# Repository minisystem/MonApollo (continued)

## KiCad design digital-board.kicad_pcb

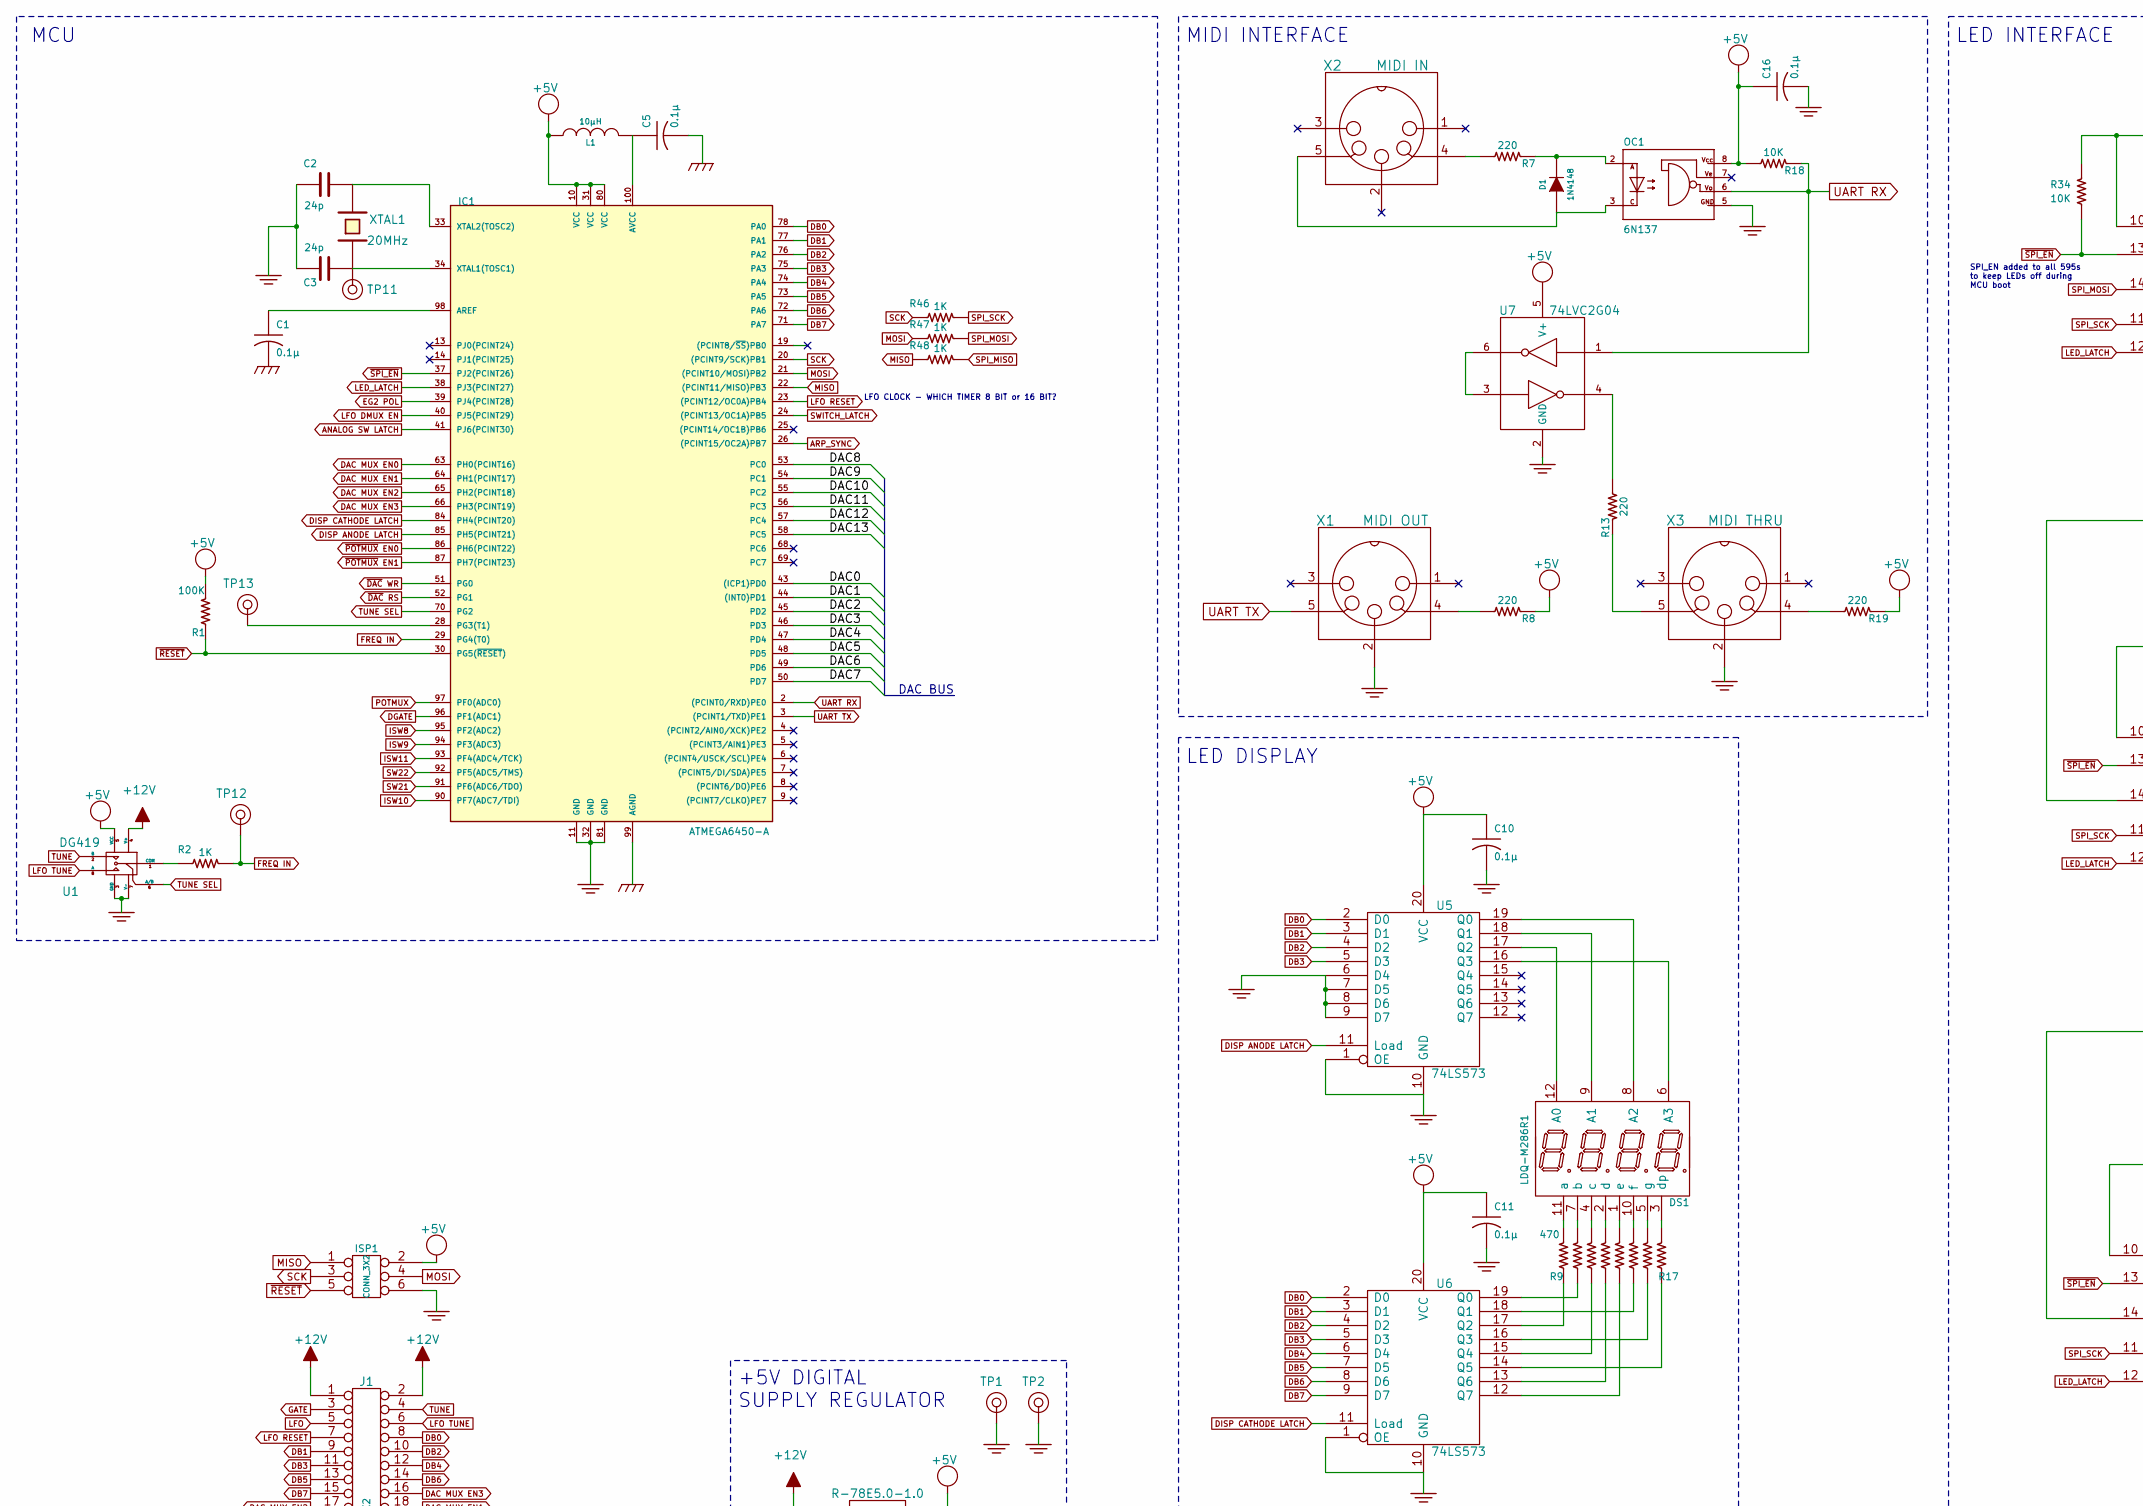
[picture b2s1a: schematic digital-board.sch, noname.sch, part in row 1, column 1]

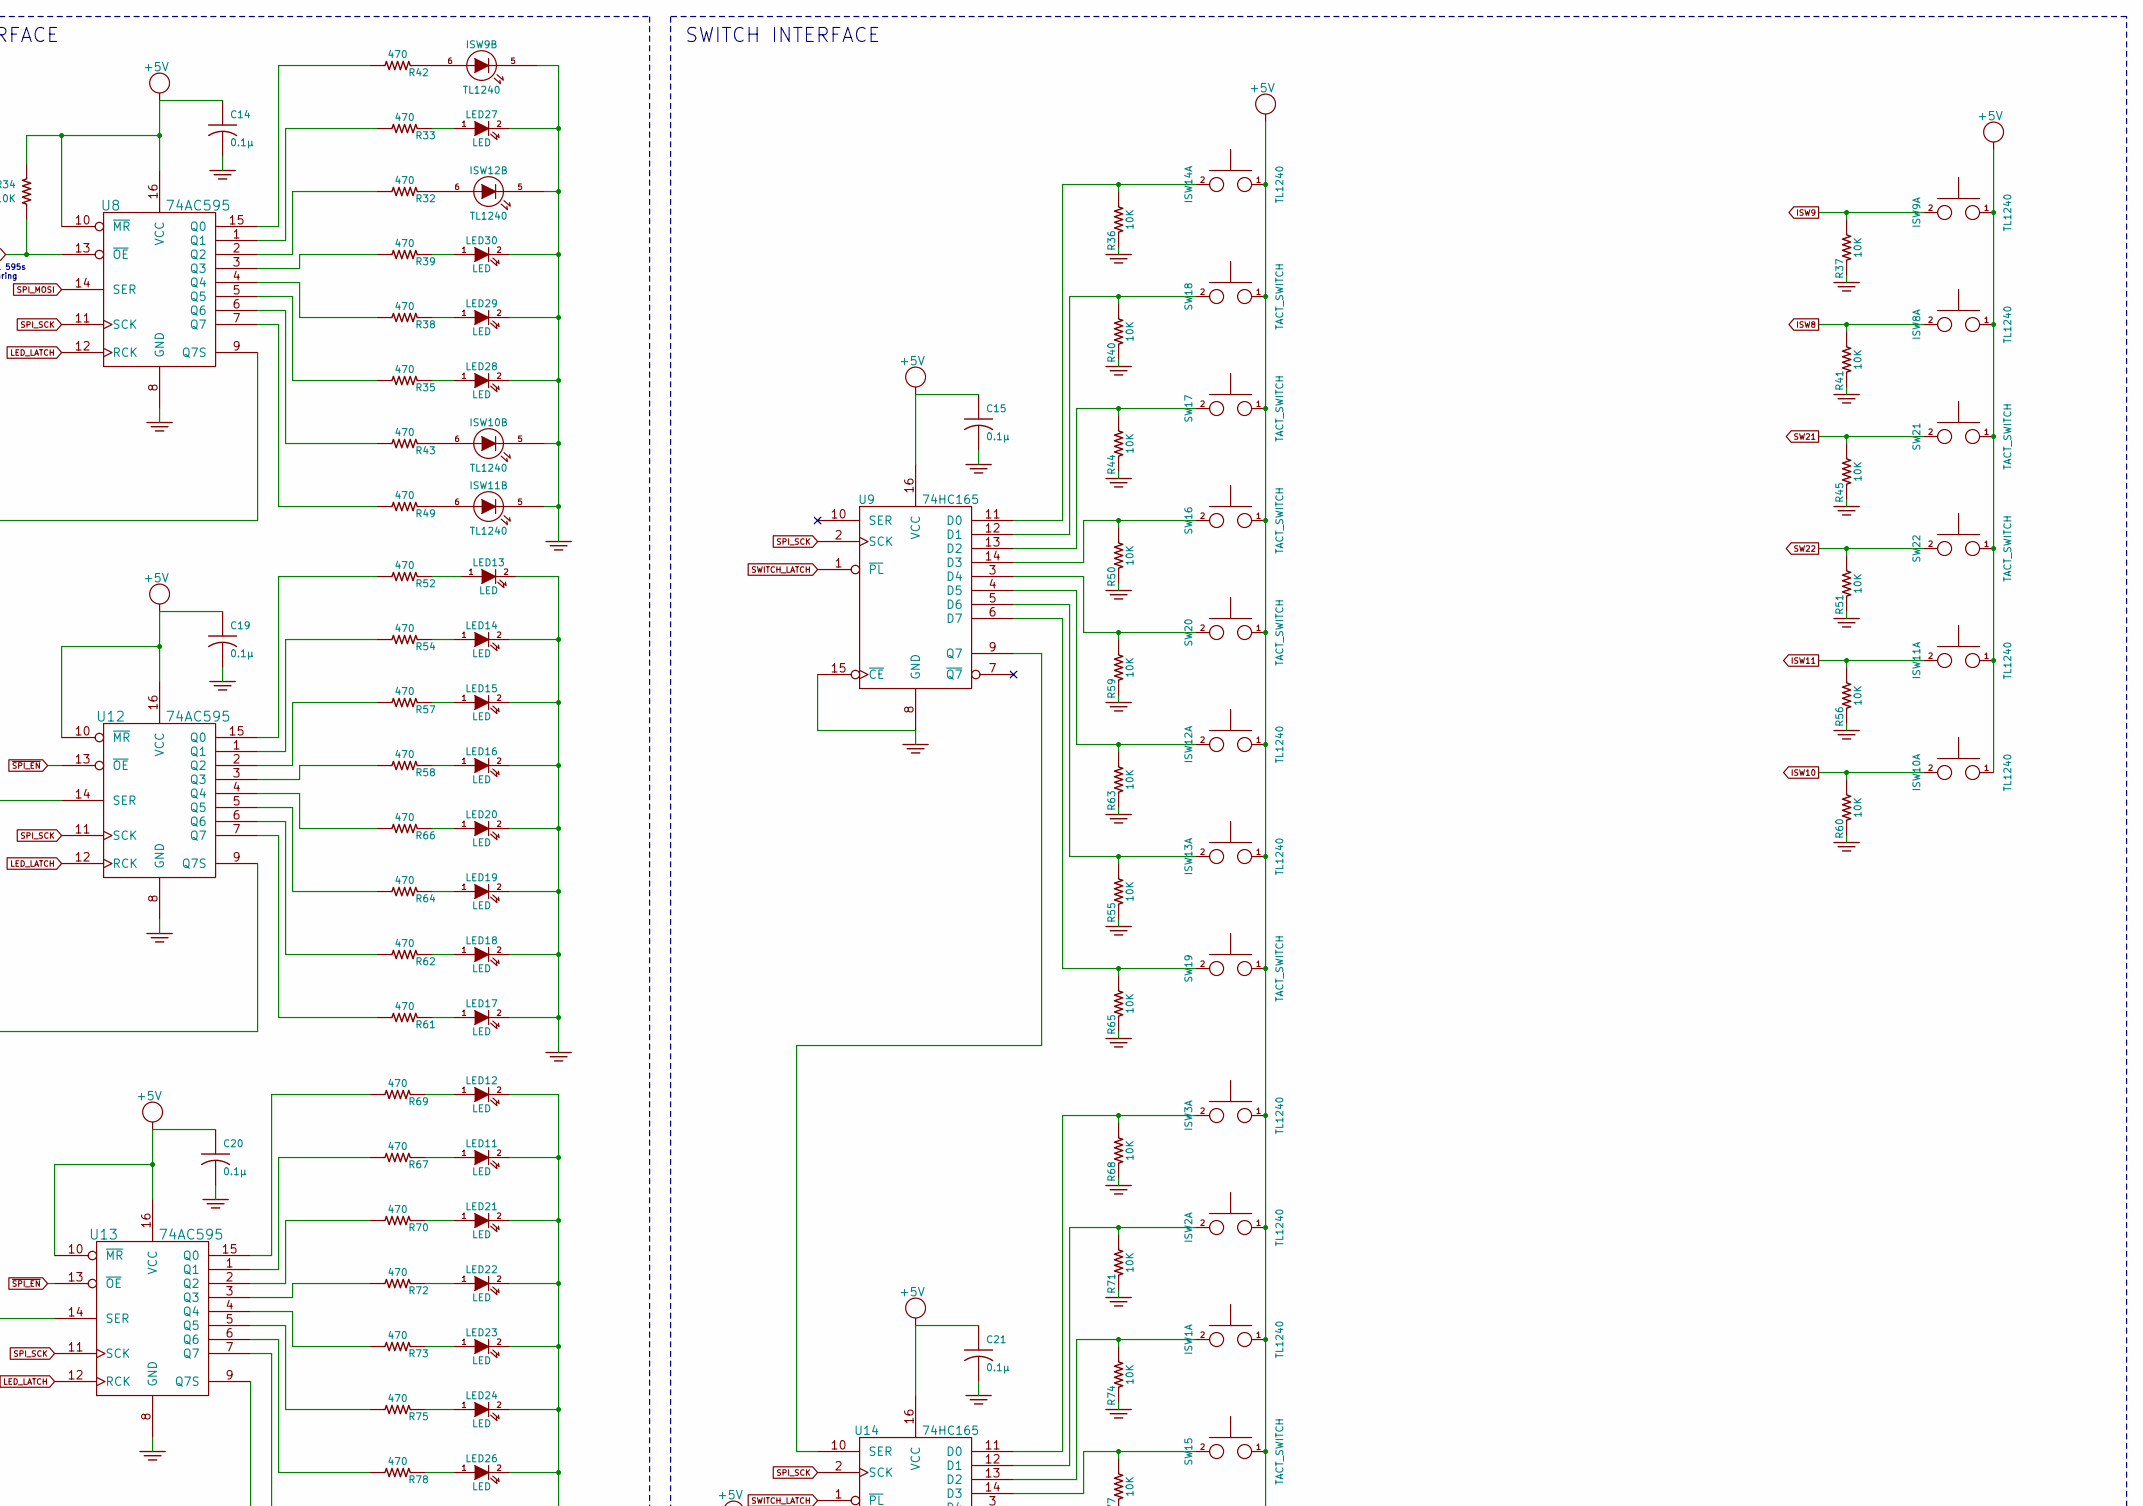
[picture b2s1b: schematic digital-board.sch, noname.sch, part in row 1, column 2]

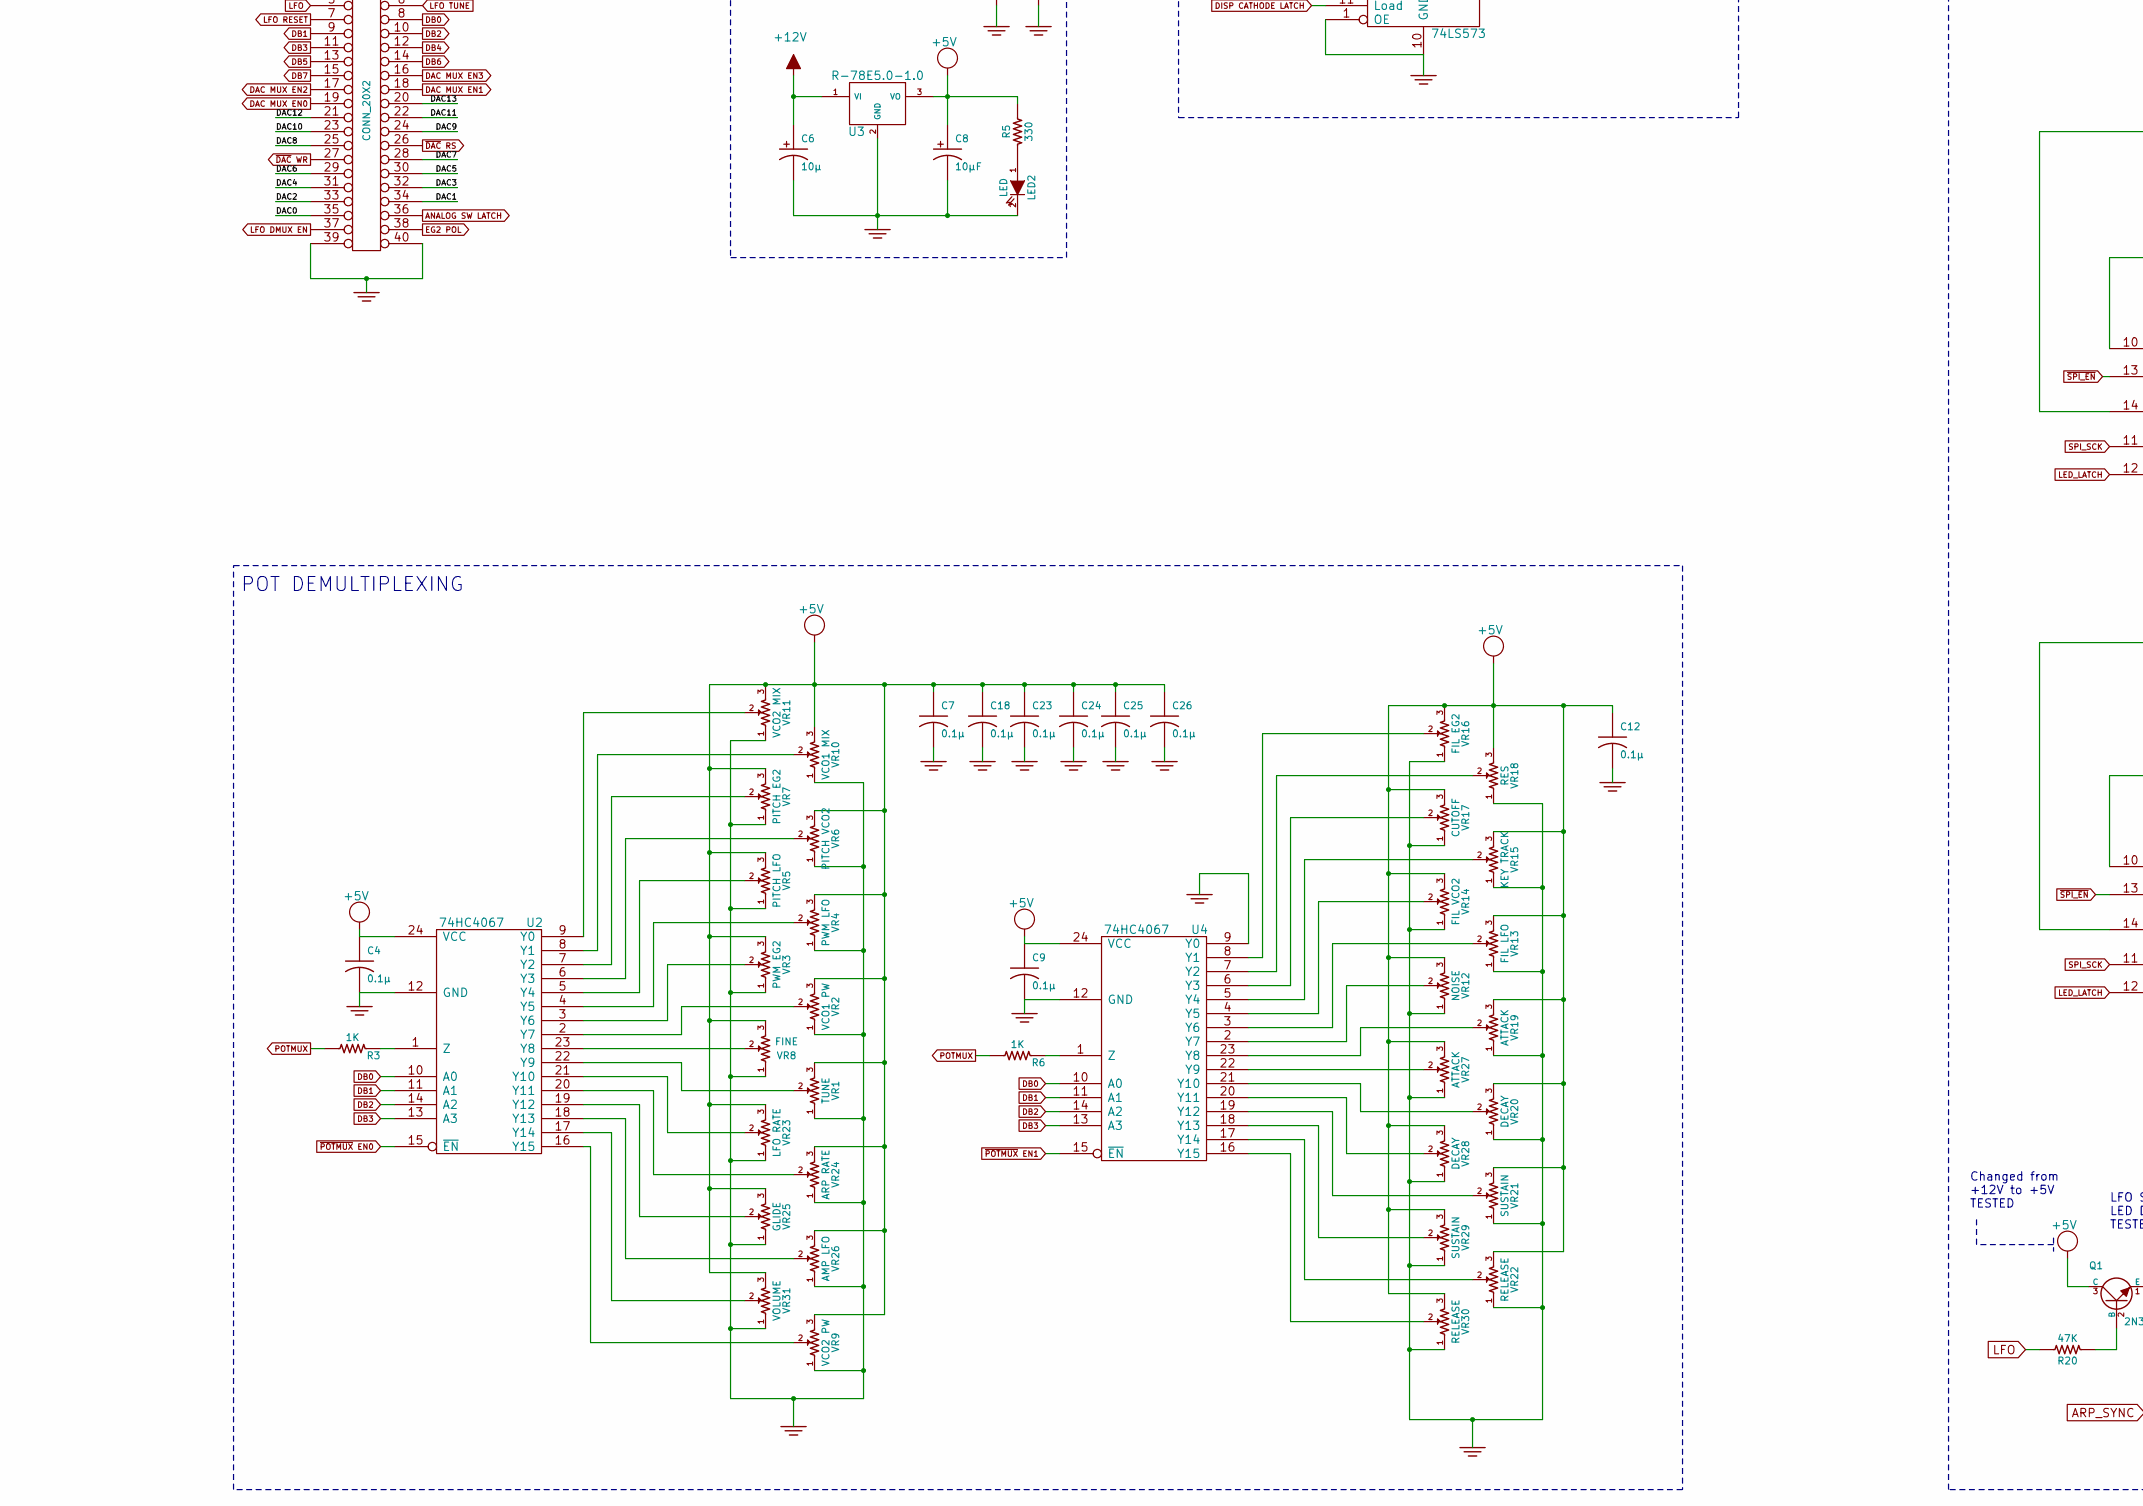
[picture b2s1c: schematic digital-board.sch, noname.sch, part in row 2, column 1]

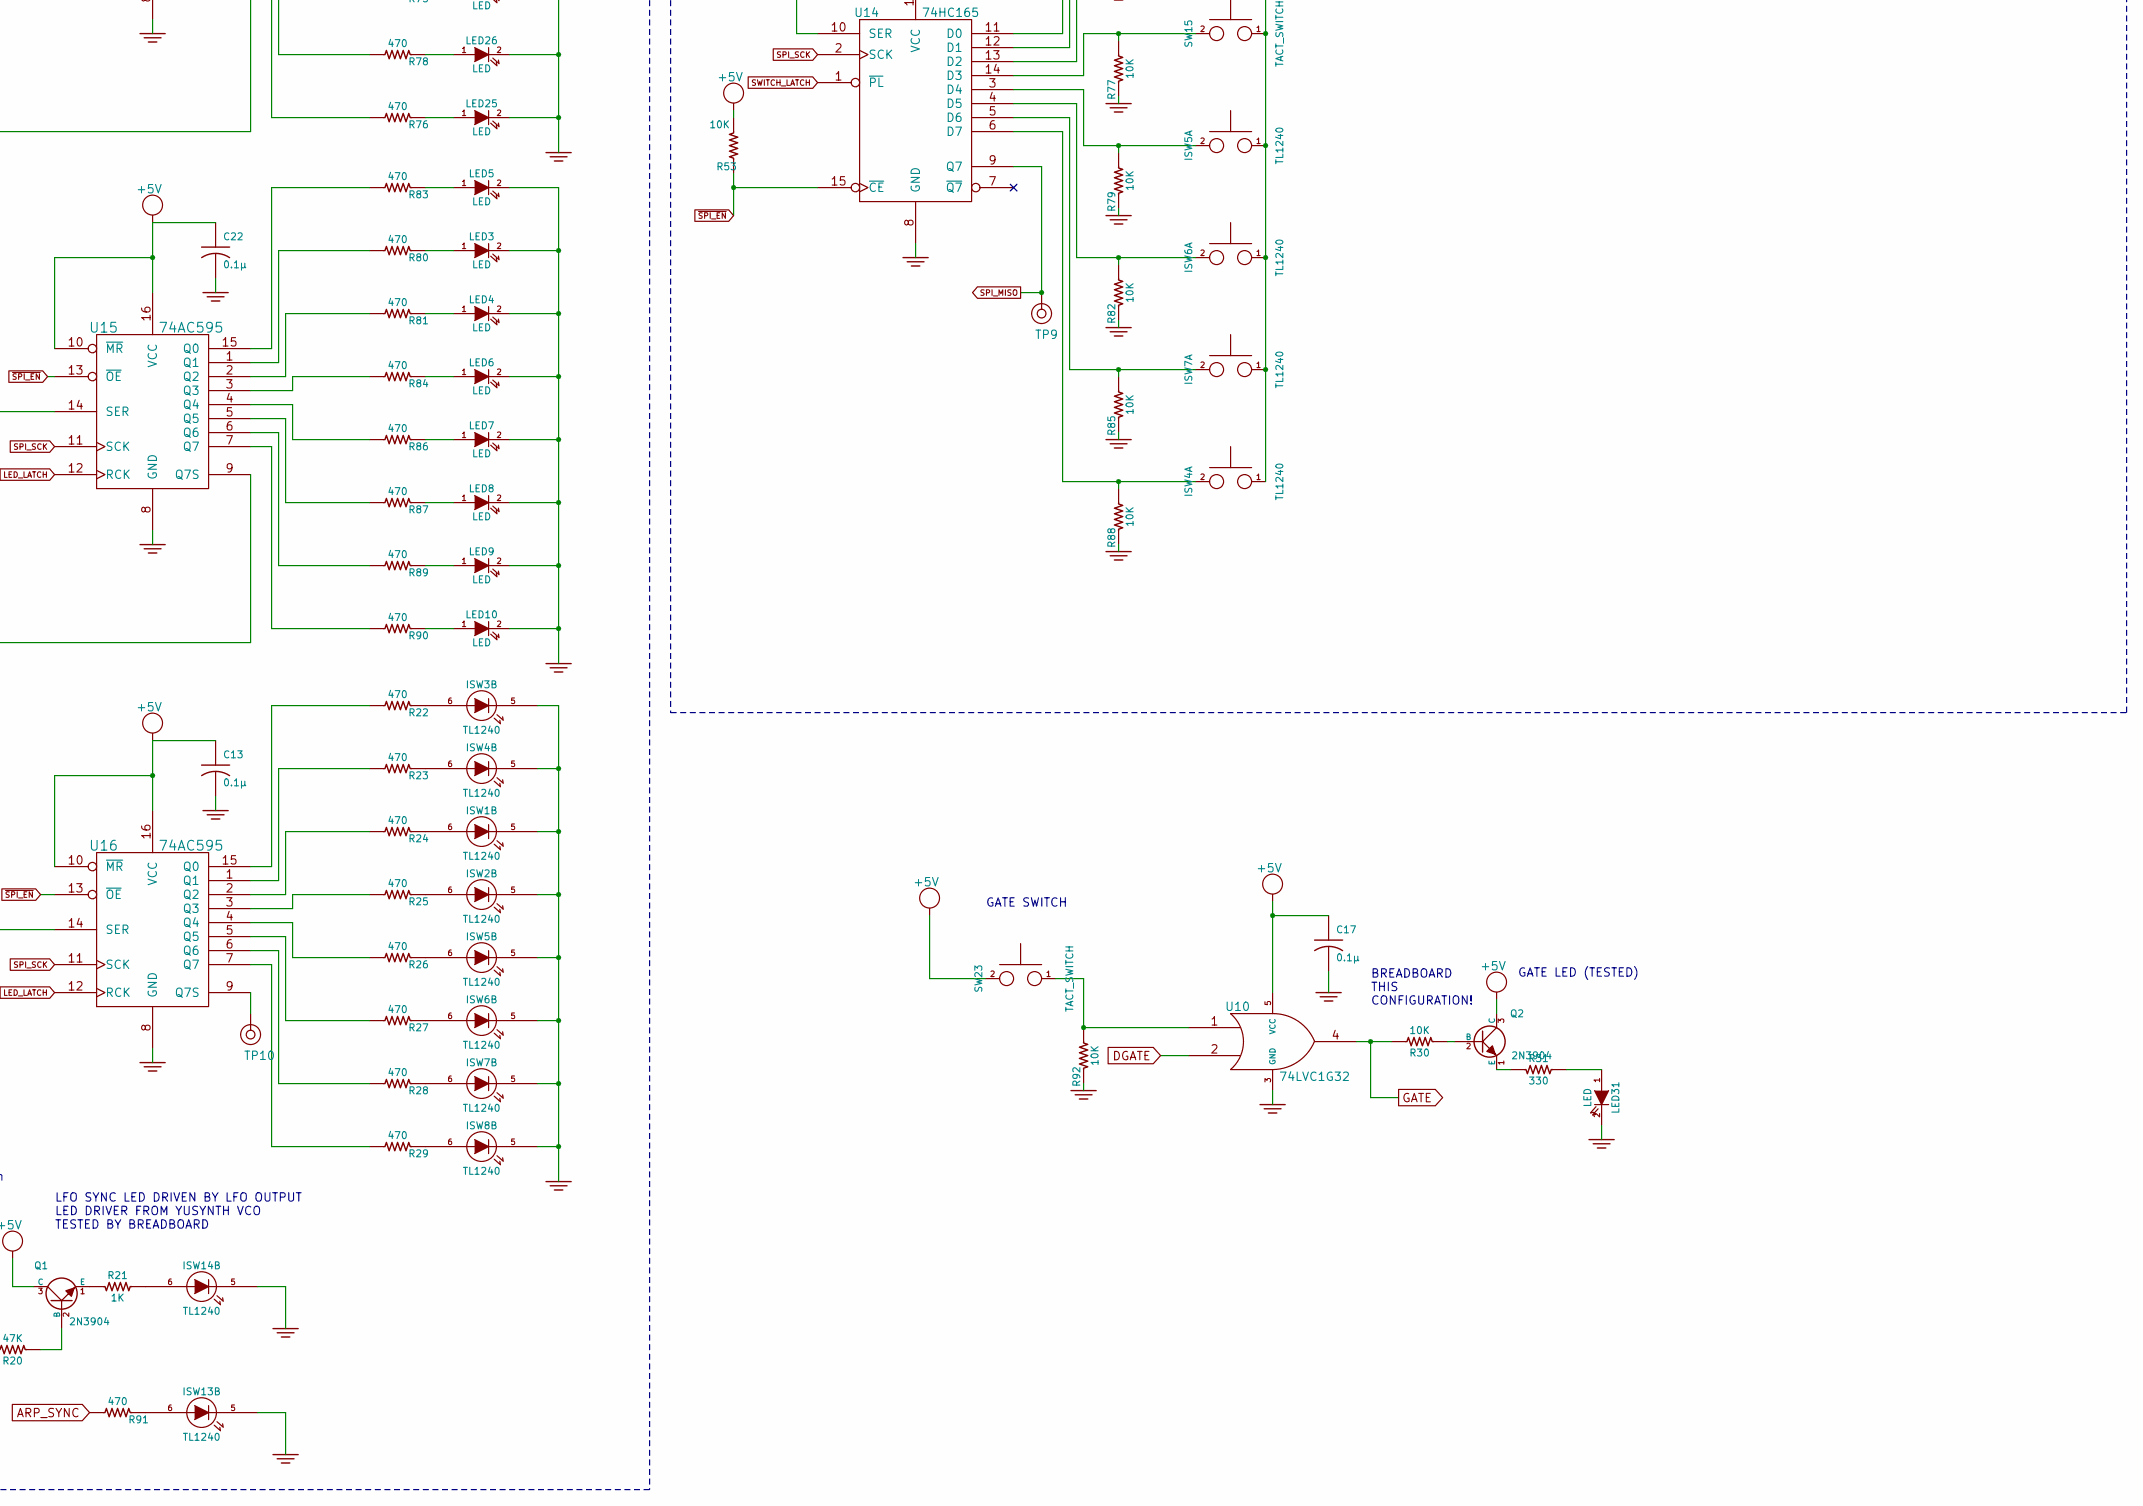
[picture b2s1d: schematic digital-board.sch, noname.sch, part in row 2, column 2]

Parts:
C1, C4, C5, C7, C9, C10, C11, C12, C13, C14, C15, C16, C17, C18, C19, C20, C21, C22, C23, C24, C25, C26: 0.1µ
C2, C3: 24p
C6: 10µ
C8: 10µF
D1: 1N4148
DS1: LDQ-M286R1; 7-segment-4-digit
IC1: ATMEGA6450-A; TQFP100
ISP1: CONN_3X2
ISW1, ISW2, ISW3, ISW4, ISW5, ISW6, ISW7, ISW8, ISW9, ISW10, ISW11, ISW12, ISW13, ISW14: TL1240
J1: CONN_20X2
L1: 10µH
LED2, LED31: LED
LED3, LED4, LED5, LED6, LED7, LED8, LED9, LED10, LED11, LED12, LED13, LED14, LED15, LED16, LED17, LED18, LED19, LED20, LED21, LED22, LED23, LED24, LED25, LED26, LED27, LED28, LED29, LED30: LED
OC1: 6N137; optocoupler-DIL08
Q1, Q2: 2N3904
R1: 100K
R2, R3, R6, R46, R47, R48: 1K
R5, R31: 330
R7, R8, R13, R19: 220
R9, R22, R23, R24, R25, R26, R27, R28, R29, R32, R33, R35, R38, R39, R42, R43, R49, R52, R54, R57, R58, R61, R62, R64, R66, R67, R69, R70, R72, R73, R75, R76, R78, R80, R81, R83, R84, R86, R87, R89, R90, R91: 470
R10, R11, R12, R14, R15, R16, R17: 560
R18, R34, R36, R37, R40, R41, R44, R45, R50, R51, R53, R55, R56, R59, R60, R63, R65, R68, R71, R74, R77, R79, R82, R85, R88, R92: 10K
R20: 47K
R21: 1K
R30: 10K
SW15, SW16, SW17, SW18, SW19, SW20, SW21, SW22, SW23: TACT_SWITCH
TP1, TP2, TP9, TP10, TP12, TP13: CONN_1
TP11: CONN_1
U1: DG419
U2, U4: 74HC4067
U3: R-78E5.0-1.0
U5, U6: 74LS573
U7: 74LVC2G04
U8, U12, U13, U15, U16: 74AC595
U9, U14: 74HC165
U10: 74LVC1G32
VR1: TUNE
VR2: VCO1 PW
VR3: PWM EG2
VR4: PWM LFO
VR5: PITCH LFO
VR6: PITCH VCO2
VR7: PITCH EG2
VR8: FINE
VR9: VCO2 PW
VR10: VCO1 MIX
VR11: VCO2 MIX
VR12: NOISE
VR13: FIL LFO
VR14: FIL VCO2
VR15: KEY TRACK
VR16: FIL EG2
VR17: CUTOFF
VR18: RES
VR19, VR27: ATTACK
VR20, VR28: DECAY
VR21, VR29: SUSTAIN
VR22, VR30: RELEASE
VR23: LFO RATE
VR24: ARP RATE
VR25: GLIDE
VR26: AMP LFO
VR31: VOLUME
X1: MIDI OUT
X2: MIDI IN
X3: MIDI THRU
XTAL1: 20MHz

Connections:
+5V: C4.1, C7.1, C8.1 (+), C9.1, C10.1, C11.1, C12.1, C13.1, C14.1, C15.1, C16.1, C17.1, C18.1, C19.1, C20.1, C21.1, C22.1, C23.1, C24.1, C25.1, C26.1, IC1.10 (VCC), IC1.31 (VCC), IC1.80 (VCC), ISP1.2, ISW1.1, ISW2.1, ISW3.1, ISW4.1, ISW5.1, ISW6.1, ISW7.1, ISW8.1, ISW9.1, ISW10.1, ISW11.1, ISW12.1, ISW13.1, ISW14.1, L1.1, OC1.8, Q1.3 (C), Q2.3 (C), R1.1, R5.2, R8.1, R18.2, R19.1, R34.1, R53.1, SW15.1, SW16.1, SW17.1, SW18.1, SW19.1, SW20.1, SW21.1, SW22.1, SW23.2, U1.5 (VCC), U2.24 (VCC), U3.3 (VO), U4.24 (VCC), U5.20 (VCC), U6.20 (VCC), U7.5 (V+), U8.10 (~MR), U8.16 (VCC), U9.16 (VCC), U10.5 (VCC), U12.10 (~MR), U12.16 (VCC), U13.10 (~MR), U13.16 (VCC), U14.16 (VCC), U15.10 (~MR), U15.16 (VCC), U16.10 (~MR), U16.16 (VCC), VR1.3, VR2.3, VR3.3, VR4.3, VR5.3, VR6.3, VR7.3, VR8.3, VR9.3, VR10.3, VR11.3, VR12.3, VR13.3, VR14.3, VR15.3, VR16.3, VR17.3, VR18.3, VR19.3, VR20.3, VR21.3, VR22.3, VR23.3, VR24.3, VR25.3, VR26.3, VR27.3, VR28.3, VR29.3, VR30.3, VR31.3
+12V: C6.1 (+), J1.1, J1.2, U1.4 (V+), U3.1 (VI)
/DAC0: IC1.43 ((ICP1)PD0), J1.35
/DAC1: IC1.44 ((INT0)PD1), J1.34
/DAC2: IC1.45 (PD2), J1.33
/DAC3: IC1.46 (PD3), J1.32
/DAC4: IC1.47 (PD4), J1.31
/DAC5: IC1.48 (PD5), J1.30
/DAC6: IC1.49 (PD6), J1.29
/DAC7: IC1.50 (PD7), J1.28
/DAC8: IC1.53 (PC0), J1.25
/DAC9: IC1.54 (PC1), J1.24
/DAC10: IC1.55 (PC2), J1.23
/DAC11: IC1.56 (PC3), J1.22
/DAC12: IC1.57 (PC4), J1.21
/DAC13: IC1.58 (PC5), J1.20
ANALOG SW LATCH: IC1.41 (PJ6(PCINT30)), J1.36
ARP_SYNC: IC1.26 ((PCINT15/OC2A)PB7), R91.2
DAC MUX EN0: IC1.63 (PH0(PCINT16)), J1.19
DAC MUX EN1: IC1.64 (PH1(PCINT17)), J1.18
DAC MUX EN2: IC1.65 (PH2(PCINT18)), J1.17
DAC MUX EN3: IC1.66 (PH3(PCINT19)), J1.16
DB0: IC1.78 (PA0), J1.8, U2.10 (A0), U4.10 (A0), U5.2 (D0), U6.2 (D0)
DB1: IC1.77 (PA1), J1.9, U2.11 (A1), U4.11 (A1), U5.3 (D1), U6.3 (D1)
DB2: IC1.76 (PA2), J1.10, U2.14 (A2), U4.14 (A2), U5.4 (D2), U6.4 (D2)
DB3: IC1.75 (PA3), J1.11, U2.13 (A3), U4.13 (A3), U5.5 (D3), U6.5 (D3)
DB4: IC1.74 (PA4), J1.12, U6.6 (D4)
DB5: IC1.73 (PA5), J1.13, U6.7 (D5)
DB6: IC1.72 (PA6), J1.14, U6.8 (D6)
DB7: IC1.71 (PA7), J1.15, U6.9 (D7)
DGATE: IC1.96 (PF1(ADC1)), U10.2
DISP ANODE LATCH: IC1.85 (PH5(PCINT21)), U5.11 (Load)
DISP CATHODE LATCH: IC1.84 (PH4(PCINT20)), U6.11 (Load)
EG2 POL: IC1.39 (PJ4(PCINT28)), J1.38
FREQ IN: IC1.29 (PG4(T0)), R2.1, TP12.1
GATE: J1.3, R30.2, U10.4
ISW8: IC1.95 (PF2(ADC2)), ISW8.2, R41.2
ISW9: IC1.94 (PF3(ADC3)), ISW9.2, R37.2
ISW10: IC1.90 (PF7(ADC7/TDI)), ISW10.2, R60.2
ISW11: IC1.93 (PF4(ADC4/TCK)), ISW11.2, R56.2
LED_LATCH: IC1.38 (PJ3(PCINT27)), U8.12 (RCK), U12.12 (RCK), U13.12 (RCK), U15.12 (RCK), U16.12 (RCK)
LFO: J1.5, R20.2
LFO DMUX EN: IC1.40 (PJ5(PCINT29)), J1.37
LFO RESET: IC1.23 ((PCINT12/OC0A)PB4), J1.7
LFO TUNE: J1.6, U1.8 (A)
MISO: IC1.22 ((PCINT11/MISO)PB3), ISP1.1, R48.2
MOSI: IC1.21 ((PCINT10/MOSI)PB2), ISP1.4, R47.2
unnamed: C1.1, IC1.98 (AREF)
unnamed: C2.2, IC1.33 (XTAL2(TOSC2)), XTAL1.2
unnamed: C3.2, IC1.34 (XTAL1(TOSC1)), TP11.1, XTAL1.1
unnamed: C5.1, IC1.100 (AVCC), L1.2
unnamed: D1.1 (A), OC1.3, X2.5
unnamed: D1.2 (K), OC1.2, R7.1
unnamed: DS1.1 (e), R14.1
unnamed: DS1.2 (d), R12.1
unnamed: DS1.3 (dp), R17.1
unnamed: DS1.4 (c), R11.1
unnamed: DS1.5 (g), R16.1
unnamed: DS1.6 (A3), U5.16 (Q3)
unnamed: DS1.7 (b), R10.1
unnamed: DS1.8 (A2), U5.19 (Q0)
unnamed: DS1.9 (A1), U5.18 (Q1)
unnamed: DS1.10 (f), R15.1
unnamed: DS1.11 (a), R9.1
unnamed: DS1.12 (A0), U5.17 (Q2)
unnamed: IC1.28 (PG3(T1)), TP13.1
unnamed: ISW1.2, R74.2, U14.13 (D2)
unnamed: ISW1.6 (A), R24.1
unnamed: ISW2.2, R71.2, U14.12 (D1)
unnamed: ISW2.6 (A), R25.1
unnamed: ISW3.2, R68.2, U14.11 (D0)
unnamed: ISW3.6 (A), R22.1
unnamed: ISW4.2, R88.2, U14.6 (D7)
unnamed: ISW4.6 (A), R23.1
unnamed: ISW5.2, R79.2, U14.3 (D4)
unnamed: ISW5.6 (A), R26.1
unnamed: ISW6.2, R82.2, U14.4 (D5)
unnamed: ISW6.6 (A), R27.1
unnamed: ISW7.2, R85.2, U14.5 (D6)
unnamed: ISW7.6 (A), R28.1
unnamed: ISW8.6 (A), R29.1
unnamed: ISW9.6 (A), R42.1
unnamed: ISW10.6 (A), R43.1
unnamed: ISW11.6 (A), R49.1
unnamed: ISW12.2, R63.2, U9.4 (D5)
unnamed: ISW12.6 (A), R32.1
unnamed: ISW13.2, R55.2, U9.5 (D6)
unnamed: ISW13.6 (A), R91.1
unnamed: ISW14.2, R36.2, U9.11 (D0)
unnamed: ISW14.6 (A), R21.2
unnamed: LED2.1 (A), R5.1
unnamed: LED3.1 (A), R80.1
unnamed: LED4.1 (A), R81.1
unnamed: LED5.1 (A), R83.1
unnamed: LED6.1 (A), R84.1
unnamed: LED7.1 (A), R86.1
unnamed: LED8.1 (A), R87.1
unnamed: LED9.1 (A), R89.1
unnamed: LED10.1 (A), R90.1
unnamed: LED11.1 (A), R67.1
unnamed: LED12.1 (A), R69.1
unnamed: LED13.1 (A), R52.1
unnamed: LED14.1 (A), R54.1
unnamed: LED15.1 (A), R57.1
unnamed: LED16.1 (A), R58.1
unnamed: LED17.1 (A), R61.1
unnamed: LED18.1 (A), R62.1
unnamed: LED19.1 (A), R64.1
unnamed: LED20.1 (A), R66.1
unnamed: LED21.1 (A), R70.1
unnamed: LED22.1 (A), R72.1
unnamed: LED23.1 (A), R73.1
unnamed: LED24.1 (A), R75.1
unnamed: LED25.1 (A), R76.1
unnamed: LED26.1 (A), R78.1
unnamed: LED27.1 (A), R33.1
unnamed: LED28.1 (A), R35.1
unnamed: LED29.1 (A), R38.1
unnamed: LED30.1 (A), R39.1
unnamed: LED31.1 (A), R31.2
unnamed: Q1.1 (E), R21.1
unnamed: Q1.2 (B), R20.1
unnamed: Q2.1 (E), R31.1
unnamed: Q2.2 (B), R30.1
unnamed: R2.2, U1.1 (COM)
unnamed: R3.1, U2.1 (Z)
unnamed: R6.1, U4.1 (Z)
unnamed: R7.2, X2.4
unnamed: R8.2, X1.4
unnamed: R9.2, U6.17 (Q2)
unnamed: R10.2, U6.19 (Q0)
unnamed: R11.2, U6.15 (Q4)
unnamed: R12.2, U6.13 (Q6)
unnamed: R13.1, X3.5
unnamed: R13.2, U7.4
unnamed: R14.2, U6.12 (Q7)
unnamed: R15.2, U6.18 (Q1)
unnamed: R16.2, U6.16 (Q3)
unnamed: R17.2, U6.14 (Q5)
unnamed: R19.2, X3.4
unnamed: R22.2, U16.15 (Q0)
unnamed: R23.2, U16.1 (Q1)
unnamed: R24.2, U16.2 (Q2)
unnamed: R25.2, U16.3 (Q3)
unnamed: R26.2, U16.4 (Q4)
unnamed: R27.2, U16.5 (Q5)
unnamed: R28.2, U16.6 (Q6)
unnamed: R29.2, U16.7 (Q7)
unnamed: R32.2, U8.2 (Q2)
unnamed: R33.2, U8.1 (Q1)
unnamed: R35.2, U8.5 (Q5)
unnamed: R38.2, U8.4 (Q4)
unnamed: R39.2, U8.3 (Q3)
unnamed: R40.2, SW18.2, U9.12 (D1)
unnamed: R42.2, U8.15 (Q0)
unnamed: R43.2, U8.6 (Q6)
unnamed: R44.2, SW17.2, U9.13 (D2)
unnamed: R49.2, U8.7 (Q7)
unnamed: R50.2, SW16.2, U9.14 (D3)
unnamed: R52.2, U12.15 (Q0)
unnamed: R54.2, U12.1 (Q1)
unnamed: R57.2, U12.2 (Q2)
unnamed: R58.2, U12.3 (Q3)
unnamed: R59.2, SW20.2, U9.3 (D4)
unnamed: R61.2, U12.7 (Q7)
unnamed: R62.2, U12.6 (Q6)
unnamed: R64.2, U12.5 (Q5)
unnamed: R65.2, SW19.2, U9.6 (D7)
unnamed: R66.2, U12.4 (Q4)
unnamed: R67.2, U13.1 (Q1)
unnamed: R69.2, U13.15 (Q0)
unnamed: R70.2, U13.2 (Q2)
unnamed: R72.2, U13.3 (Q3)
unnamed: R73.2, U13.4 (Q4)
unnamed: R75.2, U13.5 (Q5)
unnamed: R76.2, U13.7 (Q7)
unnamed: R77.2, SW15.2, U14.14 (D3)
unnamed: R78.2, U13.6 (Q6)
unnamed: R80.2, U15.1 (Q1)
unnamed: R81.2, U15.2 (Q2)
unnamed: R83.2, U15.15 (Q0)
unnamed: R84.2, U15.3 (Q3)
unnamed: R86.2, U15.4 (Q4)
unnamed: R87.2, U15.5 (Q5)
unnamed: R89.2, U15.6 (Q6)
unnamed: R90.2, U15.7 (Q7)
unnamed: R92.2, SW23.1, U10.1
unnamed: TP10.1, U16.9 (Q7S)
unnamed: U2.2 (Y7), VR2.2
unnamed: U2.3 (Y6), VR3.2
unnamed: U2.4 (Y5), VR4.2
unnamed: U2.5 (Y4), VR5.2
unnamed: U2.6 (Y3), VR6.2
unnamed: U2.7 (Y2), VR7.2
unnamed: U2.8 (Y1), VR10.2
unnamed: U2.9 (Y0), VR11.2
unnamed: U2.16 (Y15), VR9.2
unnamed: U2.17 (Y14), VR31.2
unnamed: U2.18 (Y13), VR26.2
unnamed: U2.19 (Y12), VR25.2
unnamed: U2.20 (Y11), VR24.2
unnamed: U2.21 (Y10), VR23.2
unnamed: U2.22 (Y9), VR1.2
unnamed: U2.23 (Y8), VR8.2
unnamed: U4.2 (Y7), VR12.2
unnamed: U4.3 (Y6), VR13.2
unnamed: U4.4 (Y5), VR14.2
unnamed: U4.5 (Y4), VR15.2
unnamed: U4.6 (Y3), VR17.2
unnamed: U4.7 (Y2), VR18.2
unnamed: U4.8 (Y1), VR16.2
unnamed: U4.16 (Y15), VR30.2
unnamed: U4.17 (Y14), VR22.2
unnamed: U4.18 (Y13), VR29.2
unnamed: U4.19 (Y12), VR21.2
unnamed: U4.20 (Y11), VR28.2
unnamed: U4.21 (Y10), VR20.2
unnamed: U4.22 (Y9), VR27.2
unnamed: U4.23 (Y8), VR19.2
unnamed: U7.3, U7.6
unnamed: U12.9 (Q7S), U13.14 (SER)
unnamed: U8.9 (Q7S), U12.14 (SER)
unnamed: U13.9 (Q7S), U15.14 (SER)
unnamed: U9.9 (Q7), U14.10 (SER)
unnamed: U15.9 (Q7S), U16.14 (SER)
POTMUX: IC1.97 (PF0(ADC0)), R3.2, R6.2
SCK: IC1.20 ((PCINT9/SCK)PB1), ISP1.3, R46.2
SPI_MISO: R48.1, TP9.1, U14.9 (Q7)
SPI_MOSI: R47.1, U8.14 (SER)
SPI_SCK: R46.1, U8.11 (SCK), U9.2 (SCK), U12.11 (SCK), U13.11 (SCK), U14.2 (SCK), U15.11 (SCK), U16.11 (SCK)
SW21: IC1.91 (PF6(ADC6/TDO)), R45.2, SW21.2
SW22: IC1.92 (PF5(ADC5/TMS)), R51.2, SW22.2
SWITCH_LATCH: IC1.24 ((PCINT13/OC1A)PB5), U9.1 (~PL), U14.1 (~PL)
TUNE: J1.4, U1.2 (B)
TUNE SEL: IC1.70 (PG2), U1.6 (A/B)
UART RX: IC1.2 ((PCINT0/RXD)PE0), OC1.6, R18.1, U7.1
UART TX: IC1.3 ((PCINT1/TXD)PE1), X1.5
~DAC RS: IC1.52 (PG1), J1.26
~DAC WR: IC1.51 (PG0), J1.27
~POTMUX EN0: IC1.86 (PH6(PCINT22)), U2.15 (~EN)
~POTMUX EN1: IC1.87 (PH7(PCINT23)), U4.15 (~EN)
~RESET: IC1.30 (PG5(~RESET~)), ISP1.5, R1.2
~SPI_EN: IC1.37 (PJ2(PCINT26)), R34.2, R53.2, U8.13 (~OE), U12.13 (~OE), U13.13 (~OE), U14.15 (~CE), U15.13 (~OE), U16.13 (~OE)

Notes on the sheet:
LFO SYNC LED DRIVEN BY LFO OUTPUT LED DRIVER FROM YUSYNTH VCO TESTED BY BREADBOARD
LFO CLOCK - WHICH TIMER 8 BIT or 16 BIT?
MIDI INTERFACE
POT DEMULTIPLEXING
LED DISPLAY
LED INTERFACE
SWITCH INTERFACE
MCU
+5V DIGITAL SUPPLY REGULATOR
GATE LED (TESTED)
GATE SWITCH
BREADBOARD THIS CONFIGURATION!
SPI_EN added to all 595s to keep LEDs off during MCU boot
DAC BUS
Changed from +12V to +5V TESTED

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
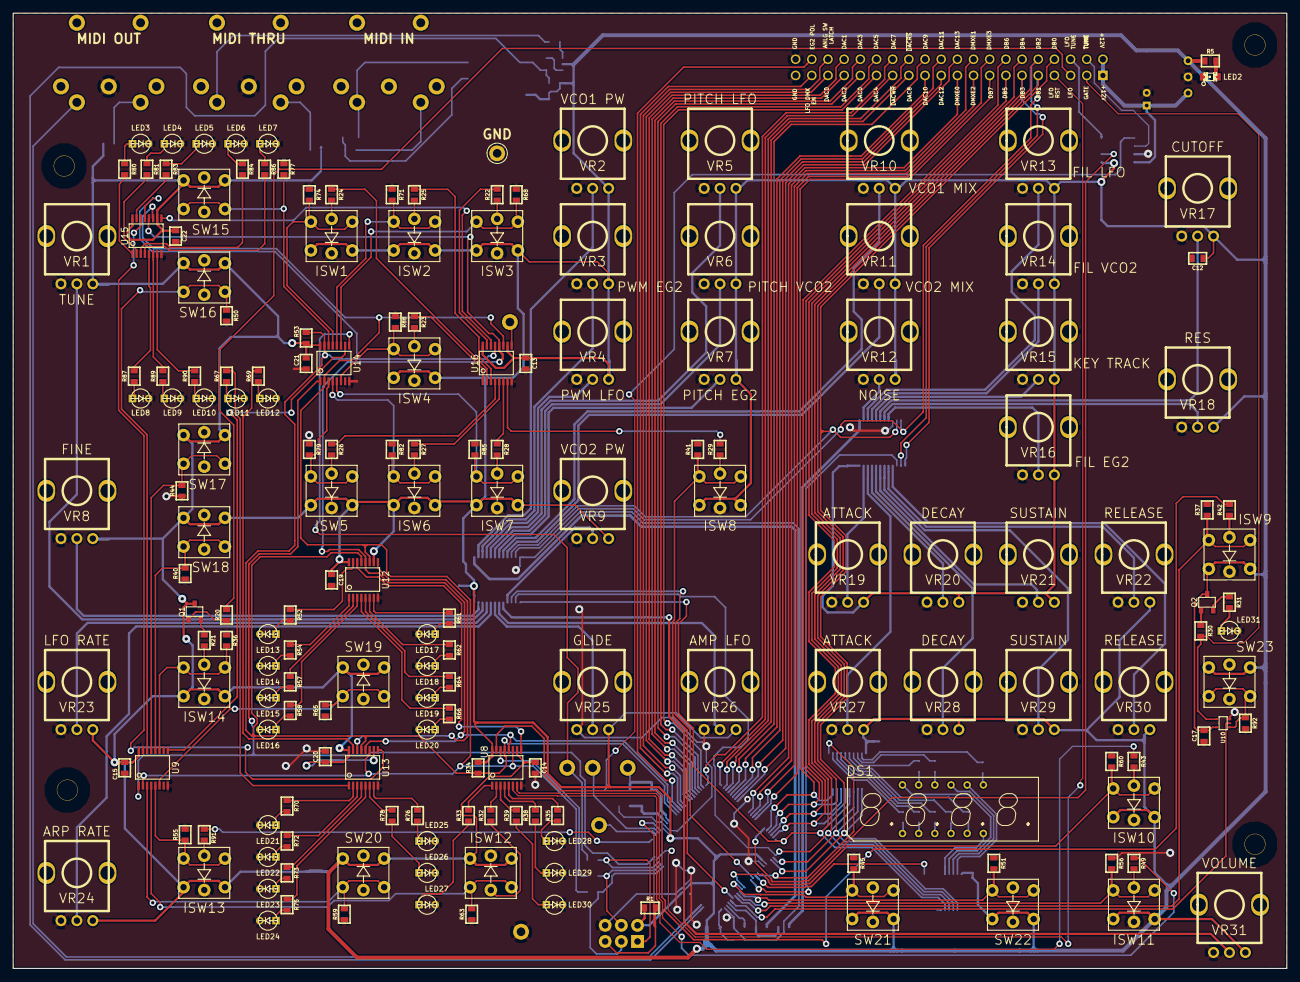
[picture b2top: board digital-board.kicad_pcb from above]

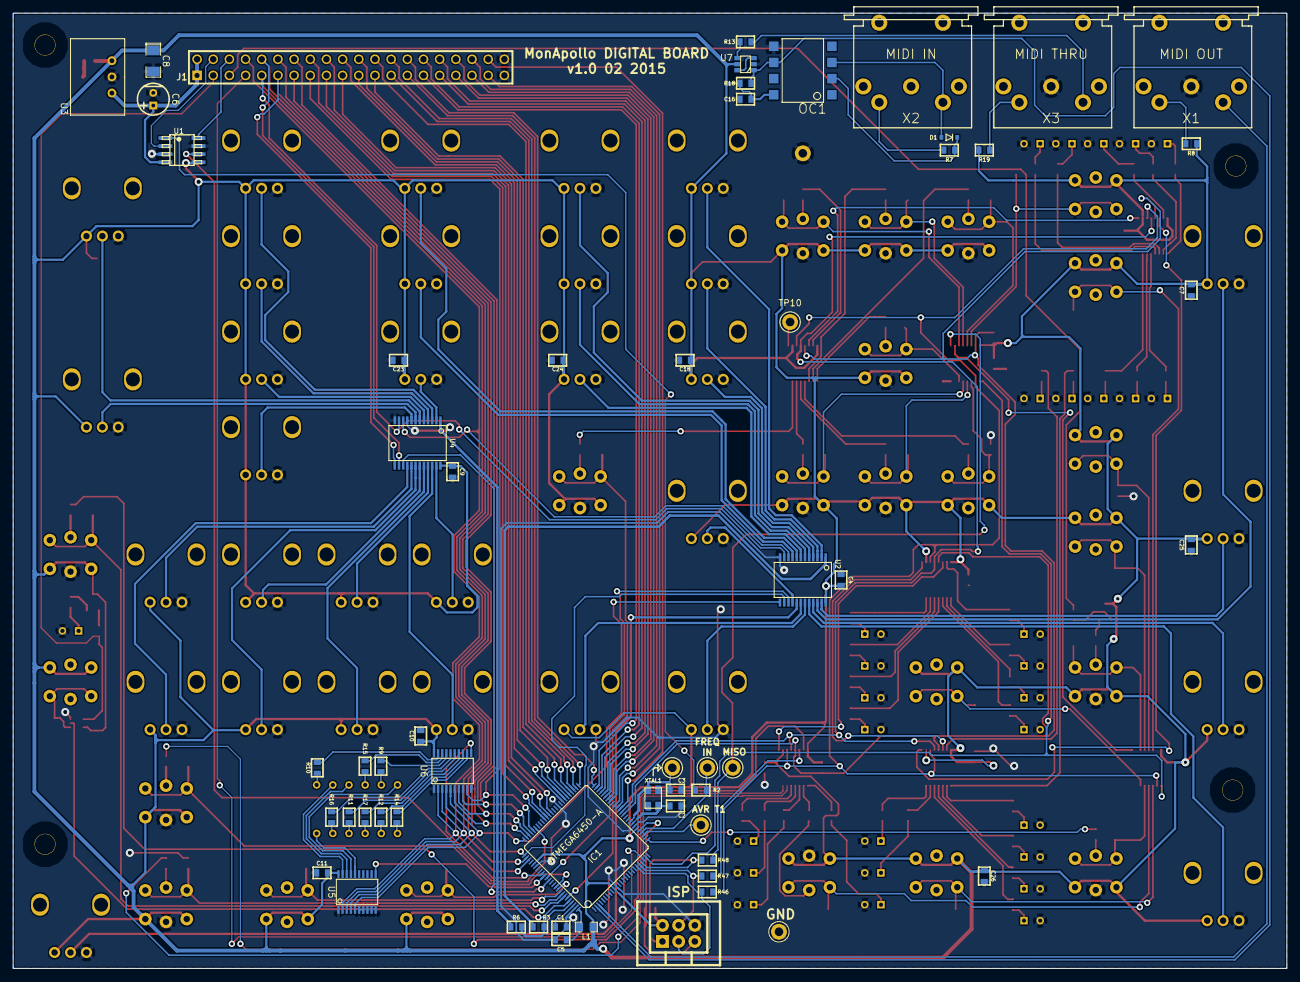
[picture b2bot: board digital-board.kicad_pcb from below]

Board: 2 copper layers, 200.0 x 150.0 mm, 240 parts (59 on the bottom side), 244 nets.

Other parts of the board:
HOLE-0.125-INCH, HOLE-0.125-INCH#2, HOLE-0.125-INCH#3, HOLE-0.125-INCH#4: VAL**; HOLE-0.125-INCH
